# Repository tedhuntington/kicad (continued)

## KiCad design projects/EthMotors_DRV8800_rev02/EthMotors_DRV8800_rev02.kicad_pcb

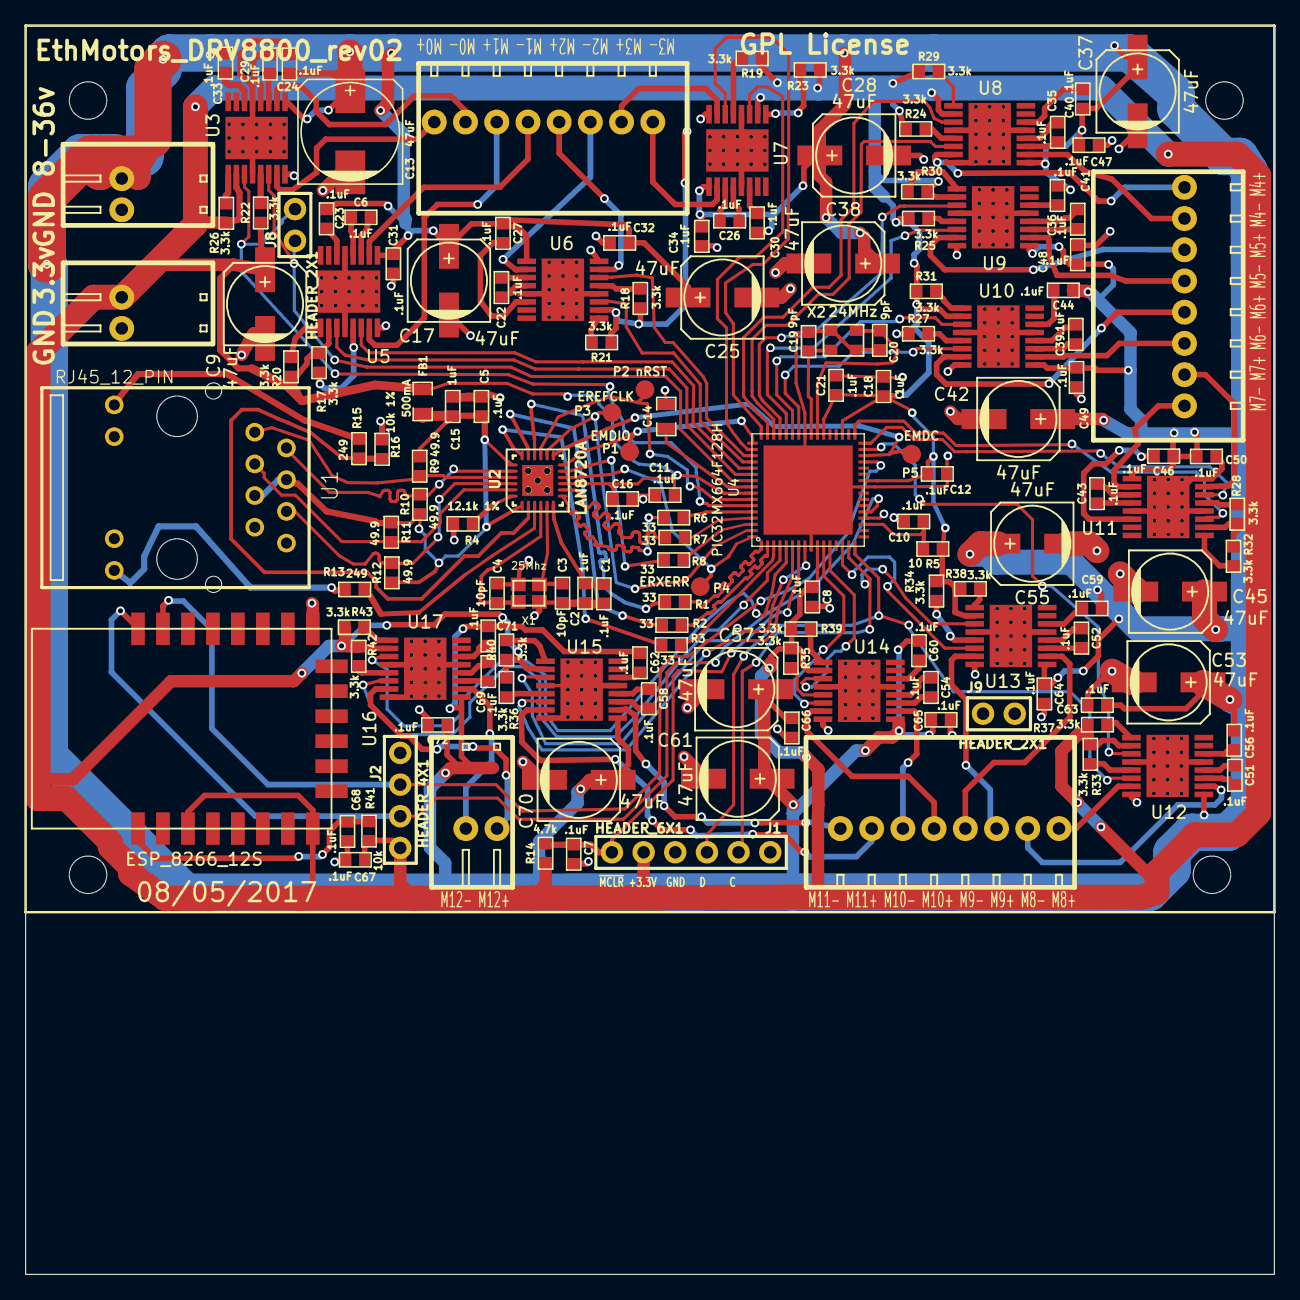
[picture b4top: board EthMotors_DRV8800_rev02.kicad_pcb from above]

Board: 2 copper layers, 100.0 x 100.0 mm, 154 parts (0 on the bottom side), 158 nets.

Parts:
C1, C5, C6, C7, C8, C10, C11, C12, C16, C18, C21, C22, C23, C24, C26, C27, C29, C30, C31, C32, C33, C34, C35, C36, C39, C40, C41, C43, C44, C46, C47, C48, C49, C50, C51, C52, C54, C56, C58, C59, C60, C62, C63, C64, C65, C66, C67, C68, C69, C71, C72: .1uF; TED_SM0603_C
C2, C15: 1uF; TED_SM0603_C
C3, C4: 10pF; TED_SM0603_C
C9, C17, C25, C28, C37, C38, C42, C45, C53, C55, C57, C61, C70: 47uF; c_elec_6.3x7.7
C13: 47uF; TED_c_elec_8x10
C14: 10uF (low ESR 1ohm); TED_SM0805_C
C19, C20: 9pF; TED_SM0603_C
FB1: 500mA; TED_SM0805_C
H1, H2, H3, H4: HOLE; TED_Hole_3mm
J1: HEADER_6X1; TED_HEADER_6x1
J2: HEADER_4X1; TED_HEADER_4x1
J3, J10: Logic DC_2.1MM; TED_TERMINAL_SPRING_2.54MM_2PIN_1989748
J4, J5, J7: TERMINAL_8X1; TED_TERMINAL_SPRING_2.54MM_8PIN_1989803
J6: Terminal_2x1; TED_TERMINAL_SPRING_2.54MM_2PIN_1989748
J8, J9: HEADER_2X1; TED_HEADER_2x1
P1: EMDIO; TED_TEST_PAD
P2: nRST; TED_TEST_PAD
P3: EREFCLK; TED_TEST_PAD
P4: ERXERR; TED_TEST_PAD
P5: EMDC; TED_TEST_PAD
R1, R2, R3, R6, R7, R8: 33; TED_SM0603_R
R4: 12.1k 1%; TED_SM0603_R
R5: 10; TED_SM0603_R
R9, R10, R11, R12: 49.9; TED_SM0603_R
R13, R15: 249; TED_SM0603_R
R14: 4.7k; TED_SM0603_R
R16: 10k 1%; TED_SM0603_R
R17, R18, R19, R20, R21, R22, R23, R24, R25, R26, R27, R28, R29, R30, R31, R32, R33, R34, R35, R36, R37, R38, R39, R40, R42, R43: 3.3k; TED_SM0603_R
R41: 10k; TED_SM0603_R
U1: RJ45_12_PIN; TED_RJ45_12pin
U2: LAN8720A; TED_QFN24+1
U3, U5, U6, U7, U8, U9, U10, U11, U12, U13, U14, U15, U17: DRV8800_PWP; TSSOP_16+1H
U4: PIC32MX664F128H; TED_QFN64+1
U16: ESP_8266_12S
X1: 25Mhz; TED_crystal_FA-20H
X2: 24MHz; crystal_TSX3225

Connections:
AVDD: C5.1, C15.1, FB1.2, R9.1, R10.1, R11.1, R12.1, U1.4, U1.5, U2.1, U2.19
ECRSDV: R8.2, U4.62
EMDC: P5.1, U2.13, U4.30
EMDIO: P1.1, U2.12, U4.49
EREFCLK: P3.1, U2.14, U4.63
ERXD0: R7.2, U4.61
ERXD1: R6.2, U4.60
ERXERR: P4.1, U2.10, U4.64
ETXD0: R2.2, U4.2
ETXD1: R3.2, U4.3
ETXEN: R1.2, U4.1
GND: C1.2, C2.2, C3.2, C4.1, C5.2, C7.2, C8.2, C9.2, C10.2, C11.2, C12.2, C13.2, C14.2, C15.2, C16.2, C17.2, C18.2, C19.2, C20.2, C21.2, C24.2, C25.2, C28.2, C31.2, C32.2, C34.2, C37.2, C38.2, C42.2, C45.2, C47.2, C48.2, C49.2, C50.2, C53.2, C55.2, C57.2, C61.2, C63.2, C64.2, C65.2, C66.2, C67.2, C68.2, C70.2, C72.2, J1.3, J2.4, J3.2, J9.1, J9.2, J10.2, R4.2, R16.2, U1.8, U1.10, U1.11, U2.25, U3.4, U3.8, U3.13, U3.17, U4.9, U4.20, U4.25, U4.41, U4.65, U5.4, U5.8, U5.13, U5.17, U6.4, U6.8, U6.13, U6.17, U7.4, U7.8, U7.13, U7.17, U8.4, U8.8, U8.13, U8.17, U9.4, U9.8, U9.13, U9.17, U10.4, U10.8, U10.13, U10.17, U11.4, U11.8, U11.13, U11.17, U12.4, U12.8, U12.13, U12.17, U13.4, U13.8, U13.13, U13.17, U14.4, U14.8, U14.13, U14.17, U15.4, U15.8, U15.13, U15.17, U16.15, U17.4, U17.8, U17.13, U17.17, X1.2, X1.4, X2.2, X2.4
GreenLED: R15.1, U1.9
M0+: J7.8, U3.7
M0-: J7.7, U3.10
M1+: J7.6, U5.7
M1-: J7.5, U5.10
M2+: J7.4, U6.7
M2-: J7.3, U6.10
M3+: J7.2, U7.7
M3-: J7.1, U7.10
M4+: J4.8, U8.7
M4-: J4.7, U8.10
M5+: J4.6, U9.7
M5-: J4.5, U9.10
M6+: J4.4, U10.7
M6-: J4.3, U10.10
M7+: J4.2, U11.7
M7-: J4.1, U11.10
M8+: J5.8, U12.7
M8-: J5.7, U12.10
M9+: J5.6, U13.7
M9-: J5.5, U13.10
M10+: J5.4, U14.7
M10-: J5.3, U14.10
M11+: J5.2, U15.7
M11-: J5.1, U15.10
M12+: J6.2, U17.7
M12-: J6.1, U17.10
unnamed: C1.1, C2.1, U2.6
unnamed: C3.1, U2.5, X1.1
unnamed: C4.2, U2.4, X1.3
unnamed: C6.1, U5.12
unnamed: C6.2, U5.11
unnamed: C10.1, R5.2, U4.19
unnamed: C14.1, U4.56
unnamed: C19.1, U4.40, X2.1
unnamed: C20.1, U4.39, X2.3
unnamed: C22.1, U6.12
unnamed: C22.2, U6.11
unnamed: C23.2, U5.14
unnamed: C26.1, U7.12
unnamed: C26.2, U7.11
unnamed: C27.2, U6.14
unnamed: C29.1, U3.12
unnamed: C29.2, U3.11
unnamed: C30.2, U7.14
unnamed: C33.2, U3.14
unnamed: C35.1, U8.12
unnamed: C35.2, U8.11
unnamed: C36.1, U9.12
unnamed: C36.2, U9.11
unnamed: C39.1, U10.12
unnamed: C39.2, U10.11
unnamed: C40.2, U8.14
unnamed: C41.2, U9.14
unnamed: C43.1, U11.12
unnamed: C43.2, U11.11
unnamed: C44.2, U10.14
unnamed: C46.2, U11.14
unnamed: C51.1, U12.12
unnamed: C51.2, U12.11
unnamed: C52.1, U13.12
unnamed: C52.2, U13.11
unnamed: C54.1, U14.12
unnamed: C54.2, U14.11
unnamed: C56.2, U12.14
unnamed: C58.1, U15.12
unnamed: C58.2, U15.11
unnamed: C59.2, U13.14
unnamed: C60.2, U14.14
unnamed: C62.2, U15.14
unnamed: C68.1, R41.2, U16.1
unnamed: C69.1, U17.12
unnamed: C69.2, U17.11
unnamed: C71.2, U17.14
unnamed: R1.1, U2.16
unnamed: R2.1, U2.17
unnamed: R3.1, U2.18
unnamed: R4.1, U2.24
unnamed: R6.1, U2.7
unnamed: R7.1, U2.8
unnamed: R8.1, U2.11
unnamed: R13.2, U2.3
unnamed: R15.2, R16.1, U2.2
unnamed: R17.2, U5.5
unnamed: R18.2, U6.5
unnamed: R19.2, U7.5
unnamed: R20.2, U5.1
unnamed: R21.2, U6.1
unnamed: R22.2, U3.5
unnamed: R23.2, U7.1
unnamed: R24.2, U8.5
unnamed: R25.2, U9.5
unnamed: R26.2, U3.1
unnamed: R27.2, U10.5
unnamed: R28.2, U11.5
unnamed: R29.2, U8.1
unnamed: R30.2, U9.1
unnamed: R31.2, U10.1
unnamed: R32.2, U11.1
unnamed: R33.2, U12.5
unnamed: R34.2, U13.5
unnamed: R35.2, U14.5
unnamed: R36.2, U15.5
unnamed: R37.2, U12.1
unnamed: R38.2, U13.1
unnamed: R39.2, U14.1
unnamed: R40.2, U15.1
unnamed: R42.2, U17.5
unnamed: R43.2, U17.1
PGEC1_RB1: J1.5, U4.15, U13.3
PGED1_RB0: J1.4, U4.16, U12.6
RB2: U4.14, U13.6
RB4: U4.12, U14.3
RB5: U4.11, U14.6
RC13: U4.47, U8.3
RC14: U4.48, U7.6
RD0: U4.46, U8.6
RD2: U4.50, U7.3
RD3: U4.51, U6.6
RD4: U4.52, U6.3
RD5: U4.53, U5.6
RD6: U4.54, U5.3
RD7: J8.2, U3.6, U4.55
RD8: U4.42, U10.6
RD9: U4.43, U10.3
RD10: U4.44, U9.6
RD11: U4.45, U9.3
RF1: J8.1, U3.3, U4.59
RF3: U4.33, U11.3
RF4: U4.31, U12.3
RF5: U4.32, U11.6
RG6: U4.4, U17.6
RG7: U4.5, U17.3
RG8: U4.6, U15.6
RG9: U4.8, U15.3
RXN: R12.2, U1.6, U2.22
RXP: R11.2, U1.3, U2.23
TXN: R10.2, U1.2, U2.20
TXP: R9.2, U1.1, U2.21
U5RX: J2.2, U4.21, U16.22
U5TX: J2.3, U4.29, U16.21
VDD: C8.1, C9.1, C11.1, C12.1, C16.1, C18.1, C21.1, C67.1, FB1.1, J1.2, J2.1, J3.1, R5.1, R14.1, R17.1, R18.1, R19.1, R20.1, R21.1, R22.1, R23.1, R24.1, R25.1, R26.1, R27.1, R28.1, R29.1, R30.1, R31.1, R32.1, R33.1, R34.1, R35.1, R36.1, R37.1, R38.1, R39.1, R40.1, R41.1, R42.1, R43.1, U2.9, U3.2, U4.10, U4.26, U4.35, U4.38, U4.57, U5.2, U6.2, U7.2, U8.2, U9.2, U10.2, U11.2, U12.2, U13.2, U14.2, U15.2, U16.3, U16.8, U17.2
VMotor: C13.1, C17.1, C23.1, C24.1, C25.1, C27.1, C28.1, C30.1, C31.1, C32.1, C33.1, C34.1, C37.1, C38.1, C40.1, C41.1, C42.1, C44.1, C45.1, C46.1, C47.1, C48.1, C49.1, C50.1, C53.1, C55.1, C56.1, C57.1, C59.1, C60.1, C61.1, C62.1, C63.1, C64.1, C65.1, C66.1, C70.1, C71.1, C72.1, J10.1, U3.9, U5.9, U6.9, U7.9, U8.9, U9.9, U10.9, U11.9, U12.9, U13.9, U14.9, U15.9, U17.9
YellowLED: R13.1, U1.12
nRST: P2.1, U2.15, U4.58
~MCLR~: C7.1, J1.1, R14.2, U4.7

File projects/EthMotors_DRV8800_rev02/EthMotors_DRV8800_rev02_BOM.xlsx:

/home/ted/kicad/projects/EthMotors_DRV8800_rev01/EthMotors_DRV8800_rev01.sch
Sun 12 Oct 2014 08:54:45 PM PDT
eeschema (2013-08-24 BZR 4298)-stable
Component Count:147
Ref | Qnty | Value | Part | Part# | Unit Cost | Total Cost | Major Distributor | Minor Distributor
C11, C21, C12, C8, C16, C5, C18, C10, C1, C7, C29, C33, C24, C30, C34, C26, C31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 | 46 | .1uF | ted_capacitors/C(SMALL) | Vj0603V104ZXAPW1BC | 0.1 | 4.6000000000000005 | Mouser
C13, C17, C22, C6, C37, C38, C39, C36, C53, C54, C55, C52, | 12 | 100uF | ted_capacitors/C_POL_SMALL | UWT1H101MNL 1GS | 0.44 | 5.28 | Mouser
C14, | 1 | 10uF (low ESR 1ohm) | ted_capacitors/C(SMALL) | LMK212F106ZG-T | 0.18 | 0.18 | Mouser
C19, C20, | 2 | 9pF | ted_capacitors/C(SMALL) | GRM1885C1H9R0DA01D | 0.1 | 0.2 | Digi-Key/Mouser
C2, C15, | 2 | 1uF | ted_capacitors/C(SMALL) | GRM188R61E105KA12D | 0.1 | 0.2 | Digi-Key
C4, C3, | 2 | 10pF | ted_capacitors/C(SMALL) | GRM1885C1H100FA01J | 0.12 | 0.24 | Mouser
C9, | 1 | 4.7uF | ted_capacitors/C(SMALL) | C0603C475K9PACTU | 0.13 | 0.13 | Mouser
FB1, | 1 | 500mA | ted_inductors/FERRITE_BEAD | MPZ2012S601A | 0.12 | 0.12 | Mouser
H1, H2, H4, H3, | 4 | HOLE | TED_holes/HOLE |  | 0 | 0
J1, | 1 | HEADER_6X1 | ted_connectors/HEADER_6X1 | 640456-6 | 0.27 | 0.27 | Mouser
J2, | 1 | JUMPER_2X1 | ted_connectors/JUMPER_2X1 | FCI 68000-102HLF | 0.19 | 0.19 | Digi-Key | AliExpress/Ebay
J3, J10, | 2 | Logic DC_2.1MM | ted_connectors/DC_2.1MM | Switchcraft RASM722X | 1.1200000000000001 | 2.2400000000000002 | Digi-Key/Mouser | AliExpress/Ebay
J7, J4, J5, | 3 | TERMINAL_8X1 | ted_connectors/TERMINAL_8X1 | 1814760 | 1.31 | 3.93 | Mouser
R12, R11, R10, R9, | 4 | 49.9 | ted_resistors/R_SMALL | ERJ-3EKF49R9V | 0.1 | 0.4 | Digi-Key
R14, | 1 | 4.7k | ted_resistors/R_SMALL | ERJ-3EKF4701V | 0.1 | 0.1 | Digi-Key
R15, R13, | 2 | 249 | ted_resistors/R_SMALL | ERJ-2RKF2490X | 0.1 | 0.2 | Digi-Key/Mouser
R16, | 1 | 10k 1% | ted_resistors/R_SMALL | ERJ-3EKF1001V | 0.1 | 0.1 | Digi-Key
R18, R19, R20, R17, R30, R31, R32, R29, R42, R43, R44, R41, | 12 | 10m | ted_resistors/R_SMALL | RL1220S-R10-F | 0.32 | 3.84 | Digi-Key
R26, R22, R27, R23, R28, R24, R25, R21, R38, R34, R39, R35, R40, R36, R37, R33,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 | 24 | 3.3k | ted_resistors/R_SMALL | ERJ-3EKF3301V | 0.1 | 2.4000000000000004 | Digi-Key
R4, | 1 | 12.1k 1% | ted_resistors/R_SMALL | ERJ-6ENF1212V | 0.1 | 0.1 | Mouser
R5, | 1 | 10 | ted_resistors/R_SMALL | CRCW060310R0FKEA | 0.1 | 0.1 | Digi-Key/Mouser
R7, R6, R2, R1, R3, R8, | 6 | 33 | ted_resistors/R_SMALL | RC0603FR-0733RL | 0.1 | 0.60000000000000009 | Digi-Key/Mouser
U1, | 1 | RJ45_12_PIN_SMD | ted_connectors/RJ45_12_PIN_SMD | HR961160C | 2.56 | 2.56 |  | AliExpress
U2, | 1 | LAN8720A | ted_ic/LAN8720A | LAN8720A | 1.49 | 1.49 | Digi-Key
U4, | 1 | PIC32MX664F128H | ted_ic/PIC32MX664F128H | PIC32MX664F128H-I/MR | 4.78 | 4.78 | MicrosoftDirect
U5, U6, U7, U3, U9, U10, U11, U8, U13, U14, U15, U12, | 12 | DRV8800_RTY | ted_ic/DRV8800_RTY | DRV8800RTYR | 2.38 | 28.56 | TI Store
X1, | 1 | 25Mhz | ted_crystals/CRYSTAL_W_2GND | FA-20H 25.0000MF20X-K3 | 0.73 | 0.73 | Mouser
X2, | 1 | 24MHz | ted_crystals/CRYSTAL_W_2GND | TSX-3225 24.0000MF20G-AC3 | 0.51 | 0.51 | Mouser
 |  |  |  |  |  | 64.05
